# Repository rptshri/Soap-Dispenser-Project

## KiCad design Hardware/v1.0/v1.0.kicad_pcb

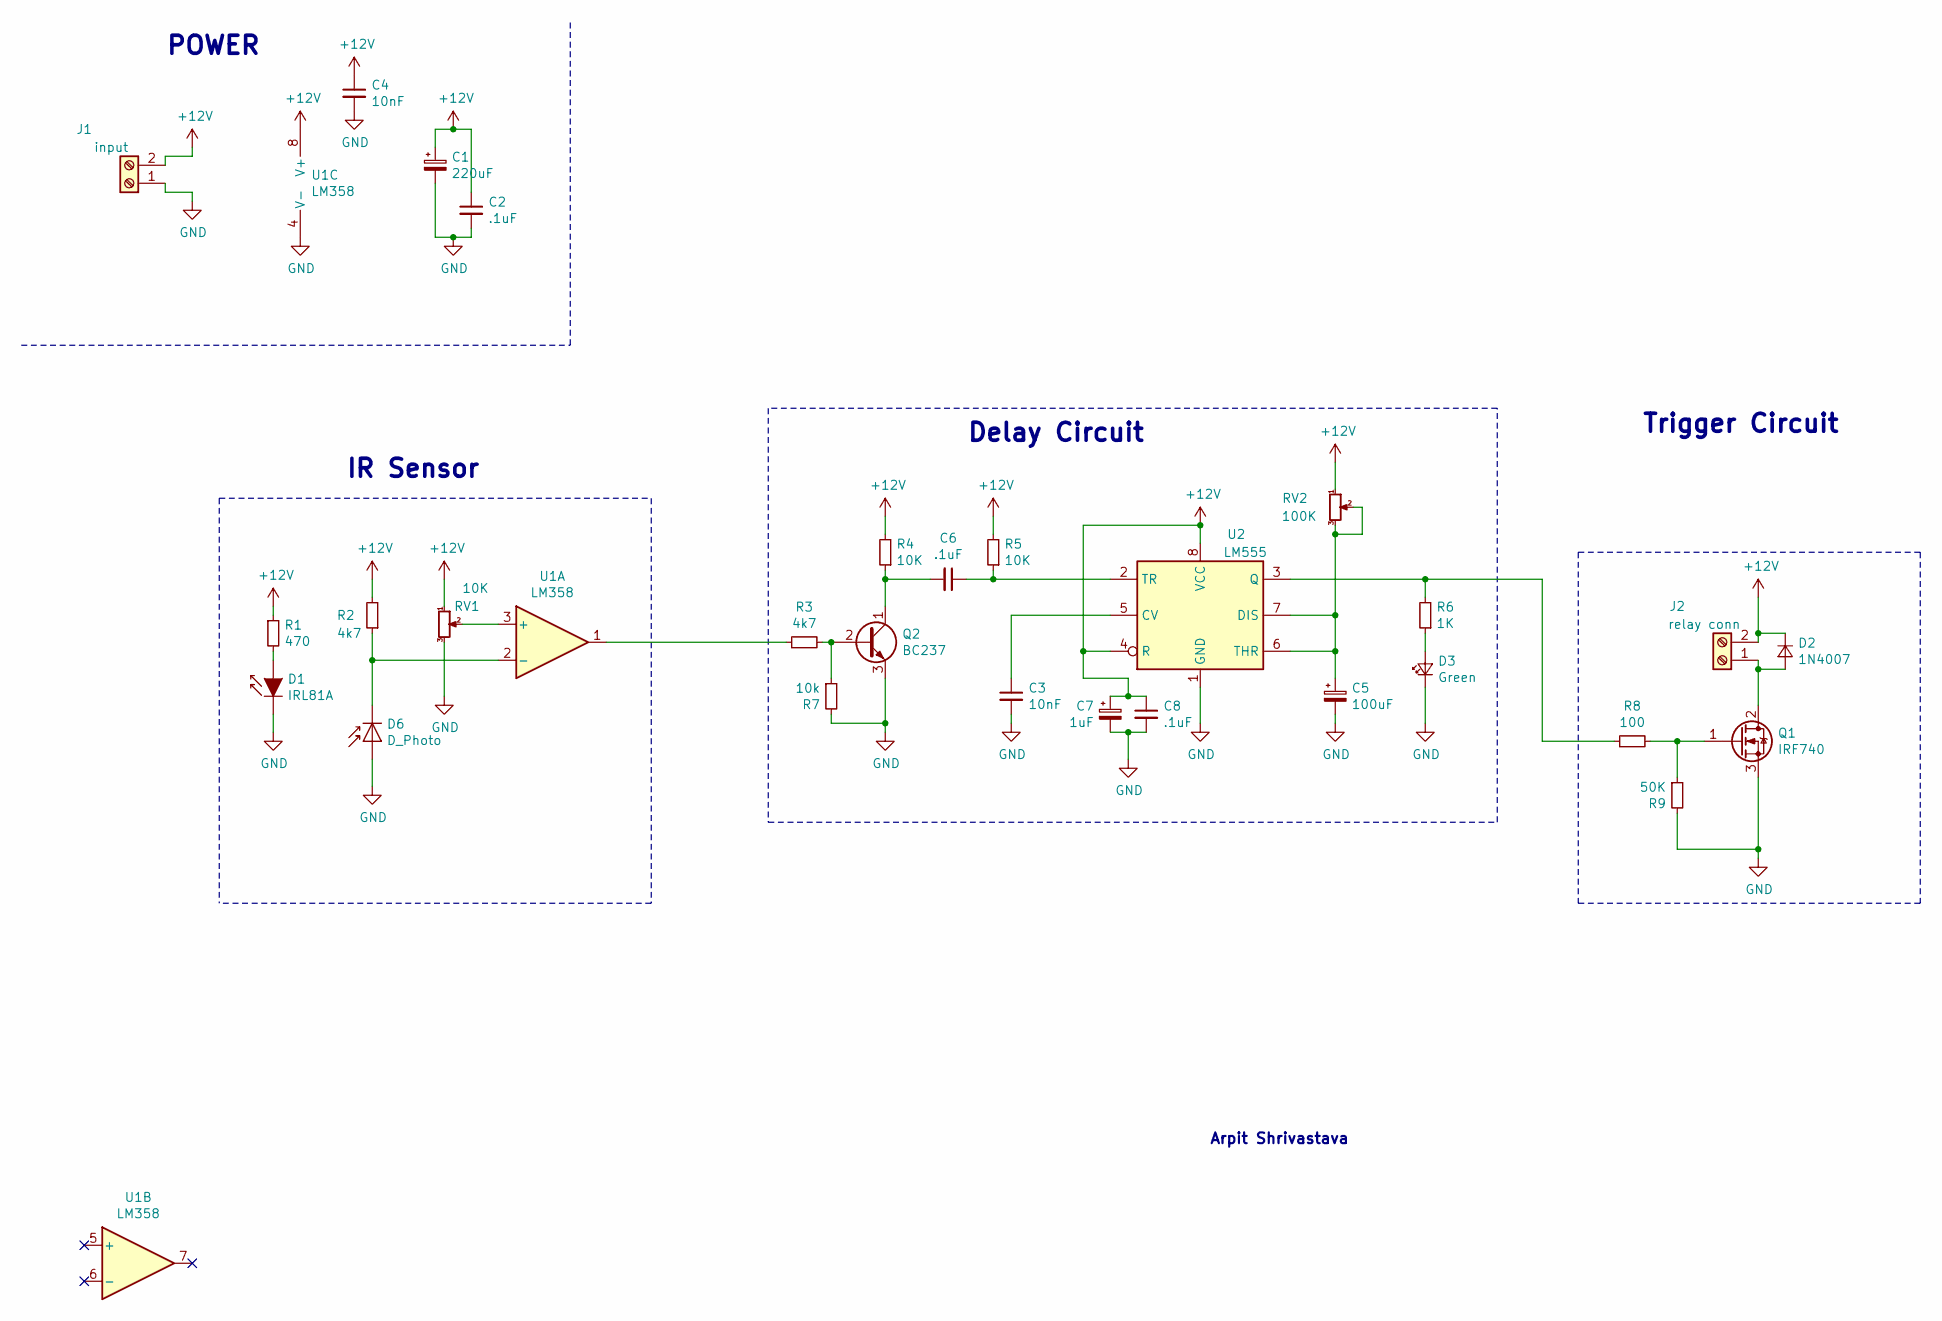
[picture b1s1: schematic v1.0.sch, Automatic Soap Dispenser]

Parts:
C1: 220uF; CP_Radial_D5.0mm_P2.50mm
C2, C8: .1uF; C_Disc_D3.4mm_W2.1mm_P2.50mm
C3, C4: 10nF; C_Disc_D3.4mm_W2.1mm_P2.50mm
C5: 100uF; CP_Radial_D5.0mm_P2.50mm
C6: .1uF; C_Disc_D3.8mm_W2.6mm_P2.50mm
C7: 1uF; CP_Radial_D5.0mm_P2.50mm
D1: IRL81A; LED_D5.0mm
D2: 1N4007; D_DO-41_SOD81_P7.62mm_Horizontal
D3: Green; LED_D5.0mm
D6: D_Photo; LED_D5.0mm
J1: input; TerminalBlock_Phoenix_MKDS-1,5-2_1x02_P5.00mm_Horizontal
J2: relay conn; TerminalBlock_Phoenix_MKDS-1,5-2_1x02_P5.00mm_Horizontal
Q1: IRF740; TO-220-3_Vertical
Q2: BC237; TO-92_HandSolder
R1: 470; R_Axial_DIN0207_L6.3mm_D2.5mm_P7.62mm_Horizontal
R2, R3: 4k7; R_Axial_DIN0207_L6.3mm_D2.5mm_P7.62mm_Horizontal
R4, R5: 10K; R_Axial_DIN0207_L6.3mm_D2.5mm_P7.62mm_Horizontal
R6: 1K; R_Axial_DIN0207_L6.3mm_D2.5mm_P7.62mm_Horizontal
R7: 10k; R_Axial_DIN0207_L6.3mm_D2.5mm_P7.62mm_Horizontal
R8: 100; R_Axial_DIN0207_L6.3mm_D2.5mm_P7.62mm_Horizontal
R9: 50K; R_Axial_DIN0207_L6.3mm_D2.5mm_P7.62mm_Horizontal
RV1: 10K; Potentiometer_Bourns_3296W_Vertical
RV2: 100K; Potentiometer_Bourns_3296W_Vertical
U1: LM358; DIP-8_W7.62mm_LongPads
U2: LM555; DIP-8_W7.62mm_LongPads

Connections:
+12V: C1.1, C2.1, C4.1, C7.1, C8.1, D2.1 (K), J1.2, J2.2, R1.1, R2.2, R4.2, R5.2, RV1.1, RV2.1, U1.8 (V+), U2.4 (R), U2.8 (VCC)
GND: C1.2, C2.2, C3.2, C4.2, C5.2, C7.2, C8.2, D1.1 (K), D3.1 (K), D6.2 (A), J1.1, Q1.3 (S), Q2.3 (E), R7.2, R9.2, RV1.3, U1.4 (V-), U2.1 (GND)
unnamed: C3.1, U2.5 (CV)
unnamed: C5.1, RV2.2, RV2.3, U2.6 (THR), U2.7 (DIS)
unnamed: C6.1, R5.1, U2.2 (TR)
unnamed: C6.2, Q2.1 (C), R4.1
unnamed: D1.2 (A), R1.2
unnamed: D2.2 (A), J2.1, Q1.2 (D)
unnamed: D3.2 (A), R6.1
unnamed: D6.1 (K), R2.1, U1.2 (-)
unnamed: Q1.1 (G), R8.2, R9.1
unnamed: Q2.2 (B), R3.2, R7.1
unnamed: R3.1, U1.1
unnamed: R6.2, R8.1, U2.3 (Q)
unnamed: RV1.2, U1.3 (+)

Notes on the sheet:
POWER
Delay Circuit
IR Sensor
Trigger Circuit
Arpit Shrivastava

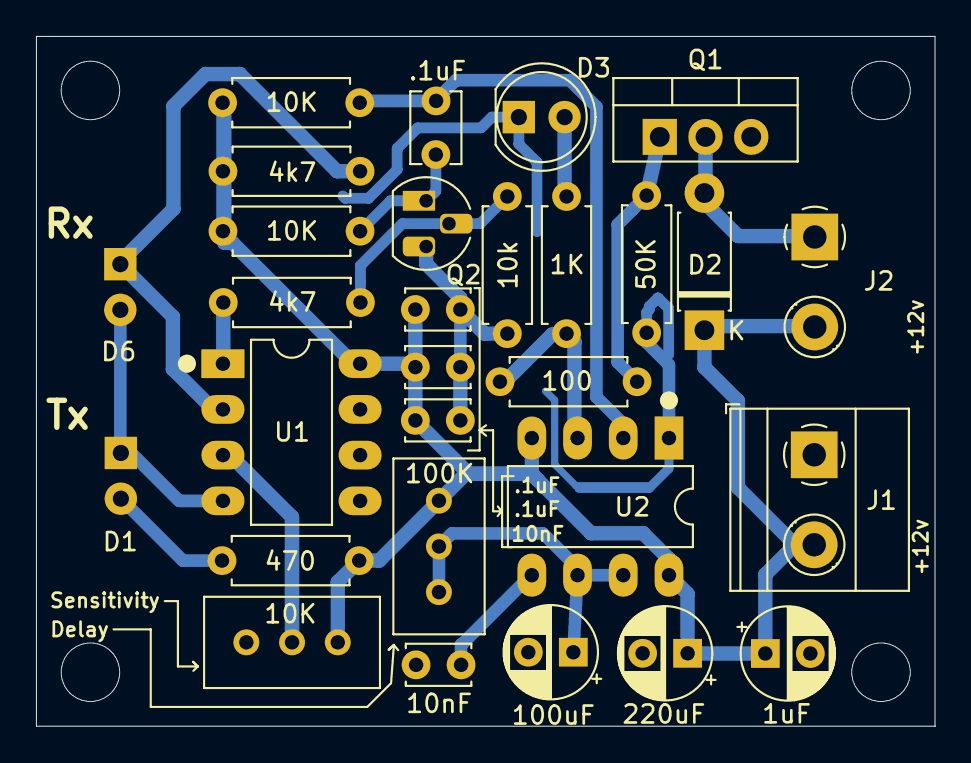
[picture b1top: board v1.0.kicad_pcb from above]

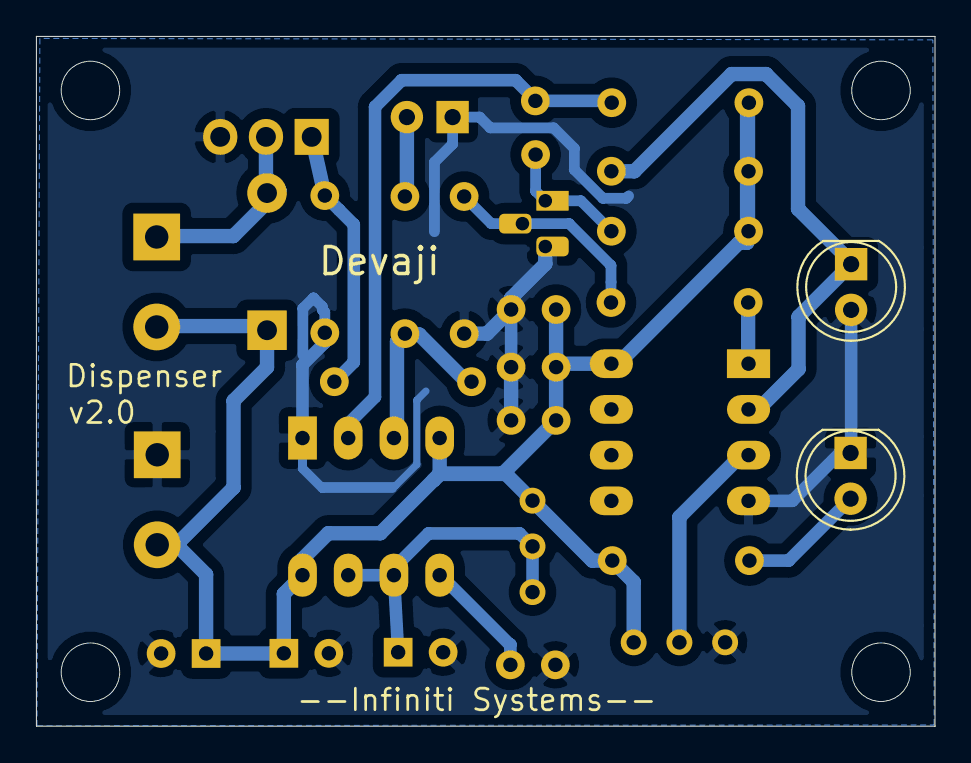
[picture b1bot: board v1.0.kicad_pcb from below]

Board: 2 copper layers, 49.9 x 38.3 mm, 29 parts (2 on the bottom side), 15 nets.

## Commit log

2020-05-18 designs updated
2020-05-24 Hardware Update
2020-05-25 [ImgBot] Optimize images
    *Total -- 658.21kb -> 511.10kb (22.35%)
    /3d files/Digital 18/hs_l.jpg -- 76.04kb -> 39.35kb (48.26%)
    /3d files/Digital 18/hs_lm.jpg -- 131.85kb -> 93.25kb (29.27%)
    /3d files/Digital 18/hs_lbl.jpg -- 450.32kb -> 378.50kb (15.95%)
2020-06-05 design with MOSFET
2020-06-25 new gerber
